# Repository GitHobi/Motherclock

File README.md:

# Motherclock
ESP8266 project to emulate a "motherclock" as used in earlier times in plants and trainstations

The old clocks can not be simply powered using voltage - they require a impulse each minute with changing polarity. 

### Work here is heavilly inspired by:

* ["Mutteruhr"](http://www.elektronik-labor.de/AVR/Mutteruhr.html)<br>The author here shows to how generate positive and negative voltage out of a MAX232 to drive a clock.
* [RTCLib](https://github.com/NeiroNx/RTCLib)<br>Provided function to communicate with a PCF8583, was light adjusted to make it more useable for my purpose

### Dependencies:

* [NtpClient](https://github.com/gmag11/NtpClient)

### Used material:

* [ntp howto](https://diyprojects.io/esp8266-web-server-part-3-recover-time-time-server-ntp/)
* [Information for PCF8583](http://www.raspberry-pi-geek.de/Magazin/2015/02/Der-Uhrenbaustein-PCF8583-am-I-2-C-Bus-des-Raspberry-Pi)
* [nodemcu tutorial](http://www.mikrocontroller-elektronik.de/nodemcu-esp8266-tutorial-wlan-board-arduino-ide/)
* [Tipps for the ESP87266](http://esp8266-server.de/Tipps.html)
* 9b-esp8266-low_power_solutions_en.pdf

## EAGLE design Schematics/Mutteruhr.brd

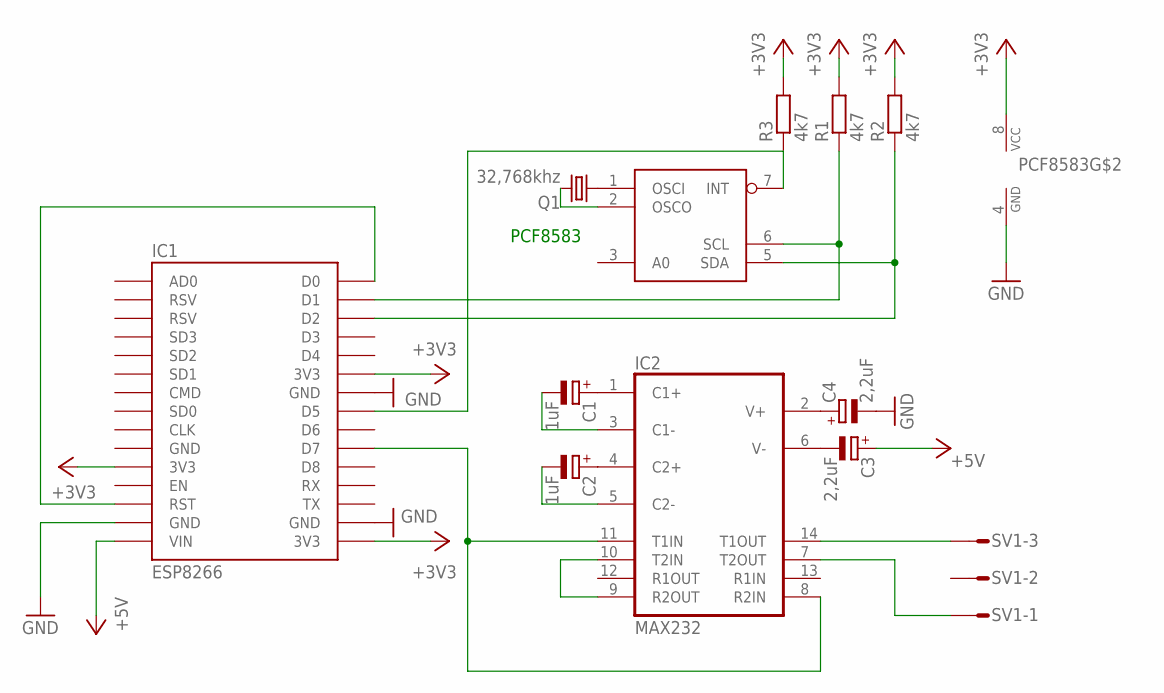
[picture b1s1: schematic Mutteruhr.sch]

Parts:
C1, C2: 1uF; E2,5-5
C3, C4: 2,2uF; E2,5-5
IC1: ESP8266; ESP12E_DEVKIT
IC2: MAX232; DIL16
PCF8583: PCF8583P; DIL08
Q1: 32,768khz; TC38H
R1, R2, R3: 4k7; 0207/10
SV1: MT6-3

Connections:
+3V3: IC1.3V3@0 (3V3), IC1.3V3@1 (3V3), IC1.3V3@2 (3V3), PCF8583.8 (VCC), R1.2, R2.2, R3.2
+5V: C3.+, IC1.VIN
CLOCK_1: IC2.14 (T1OUT), SV1.3
CLOCL_2: IC2.7 (T2OUT), SV1.1
GND: C4.-, IC1.GND@1 (GND), IC1.GND@2 (GND), IC1.GND@3 (GND), IC2.15 (GND), PCF8583.4 (GND)
INTERRUPT: IC1.D5, PCF8583.7 (INT), R3.1
MAX_OUT: IC1.D7, IC2.8 (R2IN), IC2.11 (T1IN)
unnamed: PCF8583.1 (OSCI), Q1.1
unnamed: PCF8583.2 (OSCO), Q1.2
unnamed: C2.-, IC2.5 (C2-)
unnamed: C1.-, IC2.3 (C1-)
unnamed: C1.+, IC2.1 (C1+)
unnamed: C2.+, IC2.4 (C2+)
unnamed: C3.-, IC2.6 (V-)
unnamed: C4.+, IC2.2 (V+)
unnamed: IC2.9 (R2OUT), IC2.10 (T2IN)
RESET: IC1.D0, IC1.RST
SCL: IC1.D1, PCF8583.6 (SCL), R1.1
SDA: IC1.D2, PCF8583.5 (SDA), R2.1
VCC: IC2.16 (VCC)

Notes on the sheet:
PCF8583

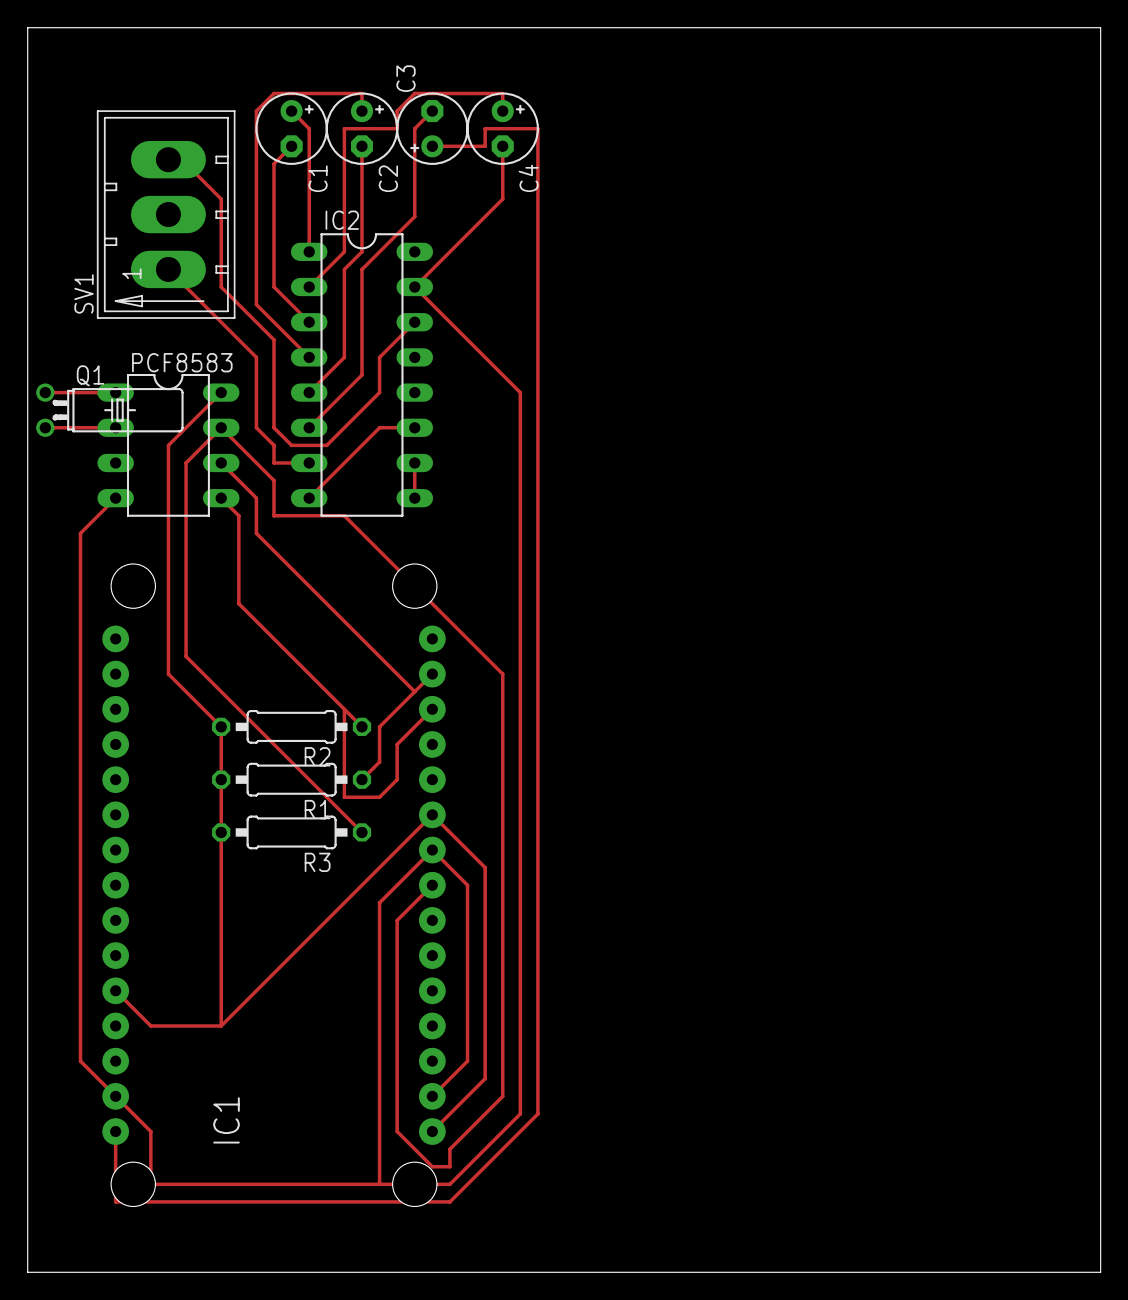
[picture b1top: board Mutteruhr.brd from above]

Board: 2 copper layers, 77.5 x 89.8 mm, 12 parts (0 on the bottom side), 19 nets.

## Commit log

2017-11-12 added support for NeoPixel to show the seconds
2017-11-13 Remove Adafruit
